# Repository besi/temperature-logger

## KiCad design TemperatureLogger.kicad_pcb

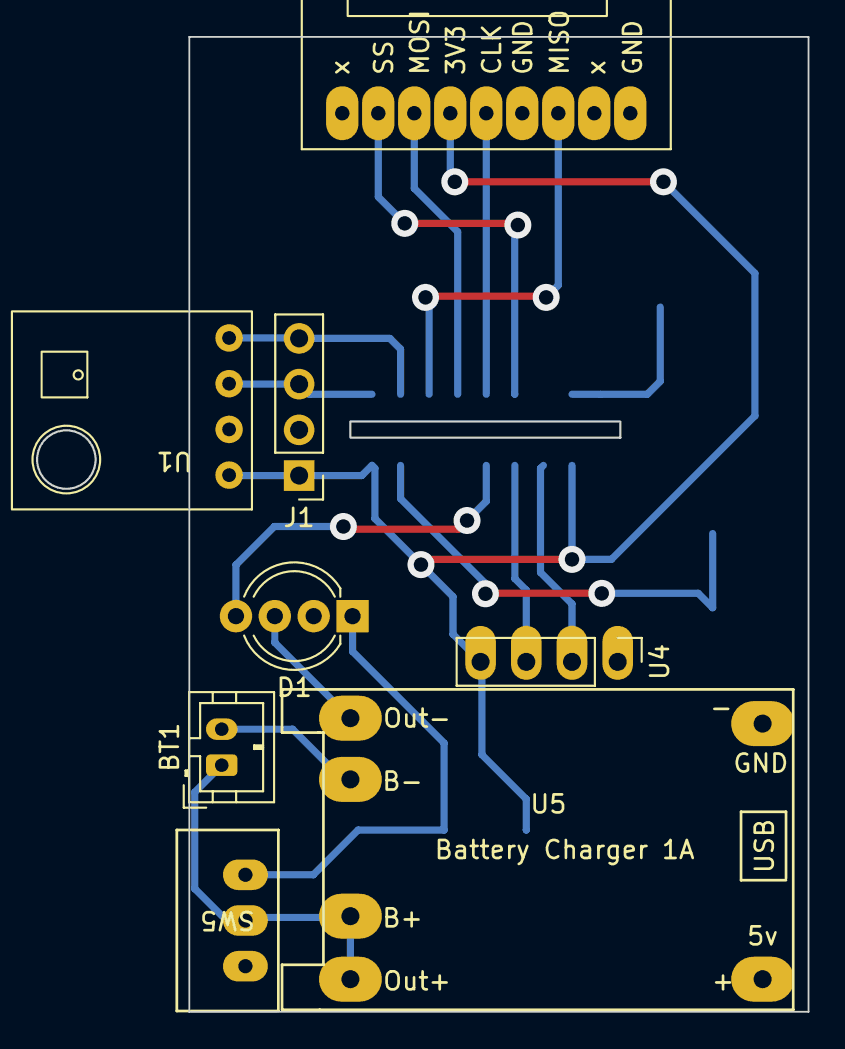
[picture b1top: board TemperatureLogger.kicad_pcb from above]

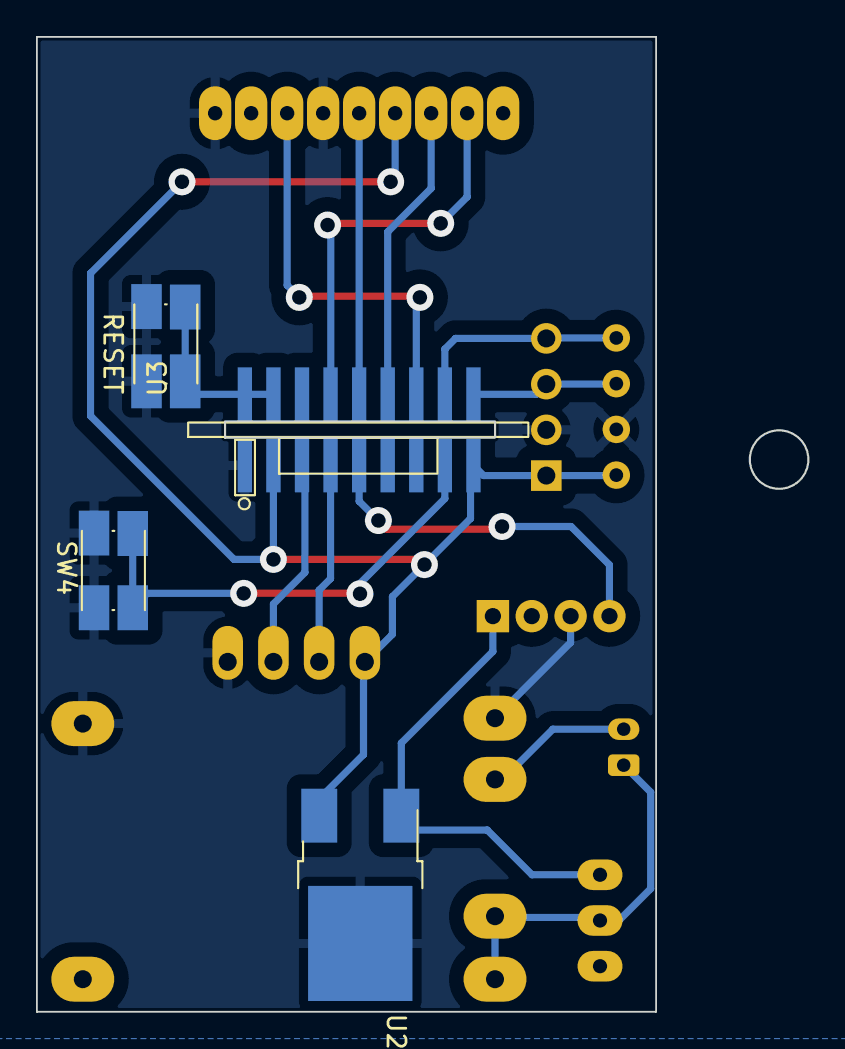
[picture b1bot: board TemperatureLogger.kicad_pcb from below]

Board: 2 copper layers, 34.4 x 54.2 mm, 12 parts (4 on the bottom side), 16 nets.

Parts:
BT1: Battery_Cell; JST_PH_B2B-PH-K_1x02_P2.00mm_Vertical
D1: WS2812B; LED_D5.0mm-4_RGB_Wide_Pins
J1: I2C; PinHeader_1x04_P2.54mm_Vertical
J3: Micro_SD_Card; sd-card
SW1: RESET; SW_Push_1P1T_NO_Vertical_Wuerth_434133025816
SW4: MODE; SW_Push_1P1T_NO_Vertical_Wuerth_434133025816
SW5: POWER; as12ap
U1: bme280
U2: UA78M33_TO252; TO-252-2
U3: esp-01m
U4: TTL; PinHeader_1x04_P2.54mm_Vertical
U5: tp4056

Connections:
+3V3: J1.1, J3.4 (VDD), U1.1 (VIN), U2.3 (VO), U3.2 (VDD), U3.9 (EN), U4.4 (VDD)
+5V: D1.1 (VDD), SW5.3 (C), U2.1 (VI)
GND: D1.3 (VSS), J1.2, J3.6 (VSS), J3.9 (SHIELD), SW1.1, SW4.1, U1.2 (GND), U2.2 (GND), U3.1 (GND), U4.1 (GND), U5.2 (IN-), U5.4 (O-)
I2C_CLK: J1.3, U1.3 (SCL), U3.10 (GP4)
I2C_SDA: J1.4, U1.4 (SDA), U3.11 (GP9)
NEOPIXEL: D1.4 (DIN), U3.5 (GP13)
unnamed: BT1.1 (+), SW5.2 (B), U5.3 (O+), U5.5 (B+)
unnamed: BT1.2 (-), U5.6 (B-)
unnamed: SW4.2, U3.8 (GP0)
unnamed: SW1.2, U3.17 (GP16), U3.18 (RST)
RX: U3.4 (GP3/RX), U4.3 (TX)
SPI_CLK: J3.5 (CLK), U3.14 (GP12)
SPI_MISO: J3.7 (DAT0), U3.12 (GP10)
SPI_MOSI: J3.3 (CMD), U3.13 (GP5)
SPI_SS: J3.2 (DAT3/CD), U3.15 (GP14)
TX: U3.3 (GP2/TX), U4.2 (RX)

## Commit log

2024-01-21 Add main components
2024-01-22 Added screenshot
2024-01-30 Add bme280 sensor and as12ap switch
2024-01-30 Update as12ap path
2024-01-30 Update sd card module
2024-01-30 First routing
2024-01-31 Addes todos
